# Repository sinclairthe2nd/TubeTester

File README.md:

# TubeTester
Im trying to build a Advanced Tube Tester controlled by a µC

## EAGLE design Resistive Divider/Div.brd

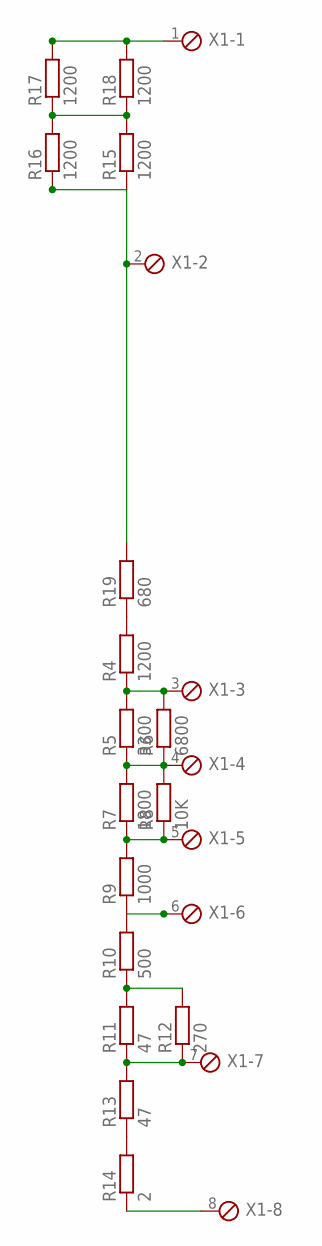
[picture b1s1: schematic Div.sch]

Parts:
R4, R15, R16, R17, R18: 1200; 0309/12
R5: 3300; 0309/10
R6: 6800; 0309/10
R7: 1800; 0309/10
R8: 10K; 0309/10
R9: 1000; 0309/10
R10: 500; 0309/10
R11, R13: 47; 0309/10
R12: 270; 0309/10
R14: 2; 0309/10
R19: 680; 0309/10
X1: MPT8; 8POL254

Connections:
unnamed: R17.2, R18.2, X1.1
unnamed: R15.1, R16.1, R19.2, X1.2
unnamed: R4.1, R5.2, R6.2, X1.3
unnamed: R14.1, X1.8
unnamed: R5.1, R6.1, R7.2, R8.2, X1.4
unnamed: R7.1, R8.1, R9.2, X1.5
unnamed: R9.1, R10.2, X1.6
unnamed: R10.1, R11.2, R12.2
unnamed: R11.1, R12.1, R13.2, X1.7
unnamed: R13.1, R14.2
unnamed: R4.2, R19.1
unnamed: R15.2, R16.2, R17.1, R18.1

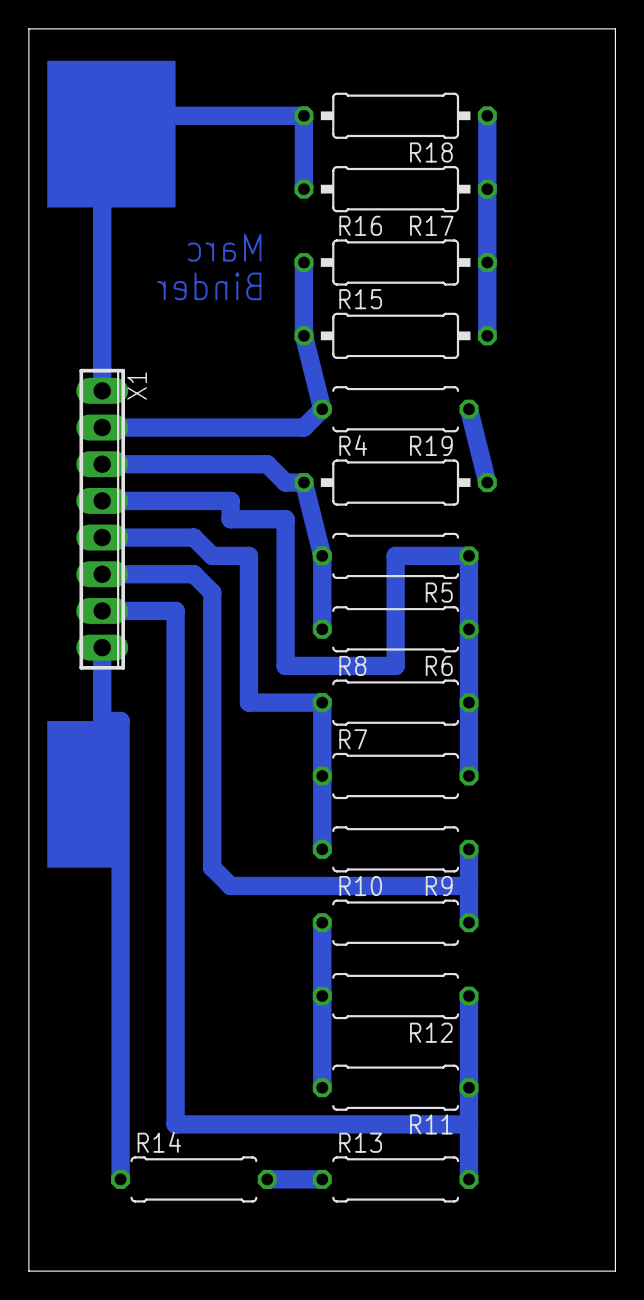
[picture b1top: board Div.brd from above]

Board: 2 copper layers, 40.6 x 86.0 mm, 17 parts (0 on the bottom side), 12 nets.

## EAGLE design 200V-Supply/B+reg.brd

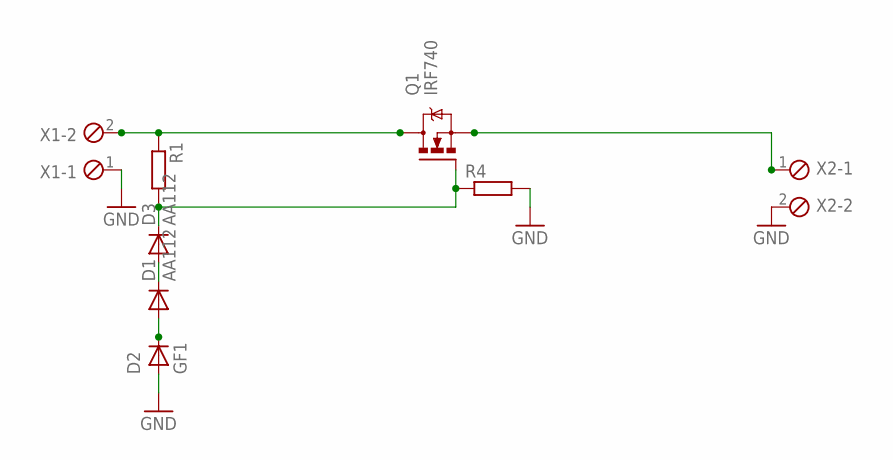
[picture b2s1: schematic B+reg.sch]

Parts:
D1, D3: AA112; DO07
D2: GF1; SMA-DO214AC
Q1: IRF740; TO220BV
R1, R4: R-EU_R0805; R0805
X1, X2: MPT2; 2POL254

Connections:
GND: D2.A, R4.2, X1.1, X2.2
unnamed: D1.A, D2.K (C)
unnamed: D1.C, D3.A
unnamed: Q1.D, R1.1, X1.2
unnamed: D3.C, Q1.G, R1.2, R4.1
unnamed: Q1.S, X2.1

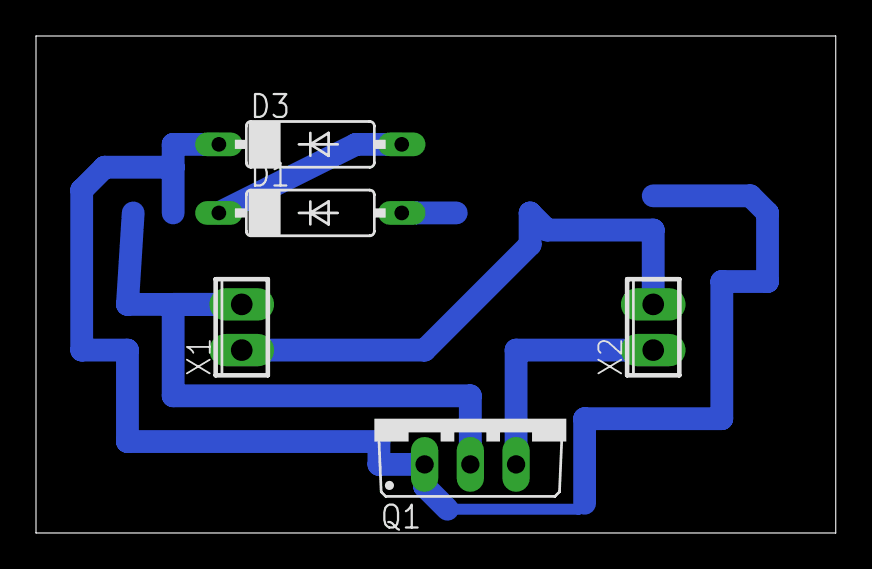
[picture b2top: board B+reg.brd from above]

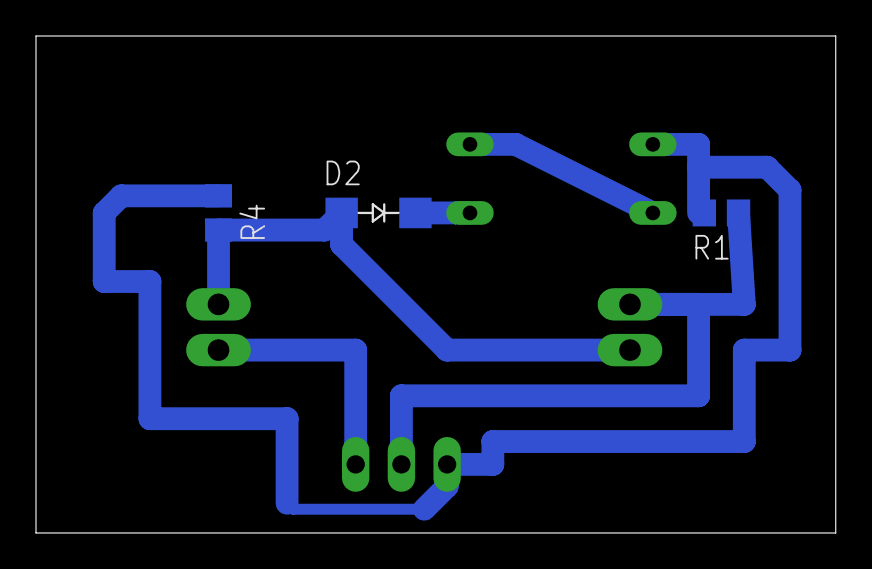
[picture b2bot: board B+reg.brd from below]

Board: 2 copper layers, 44.4 x 27.6 mm, 8 parts (3 on the bottom side), 6 nets.
